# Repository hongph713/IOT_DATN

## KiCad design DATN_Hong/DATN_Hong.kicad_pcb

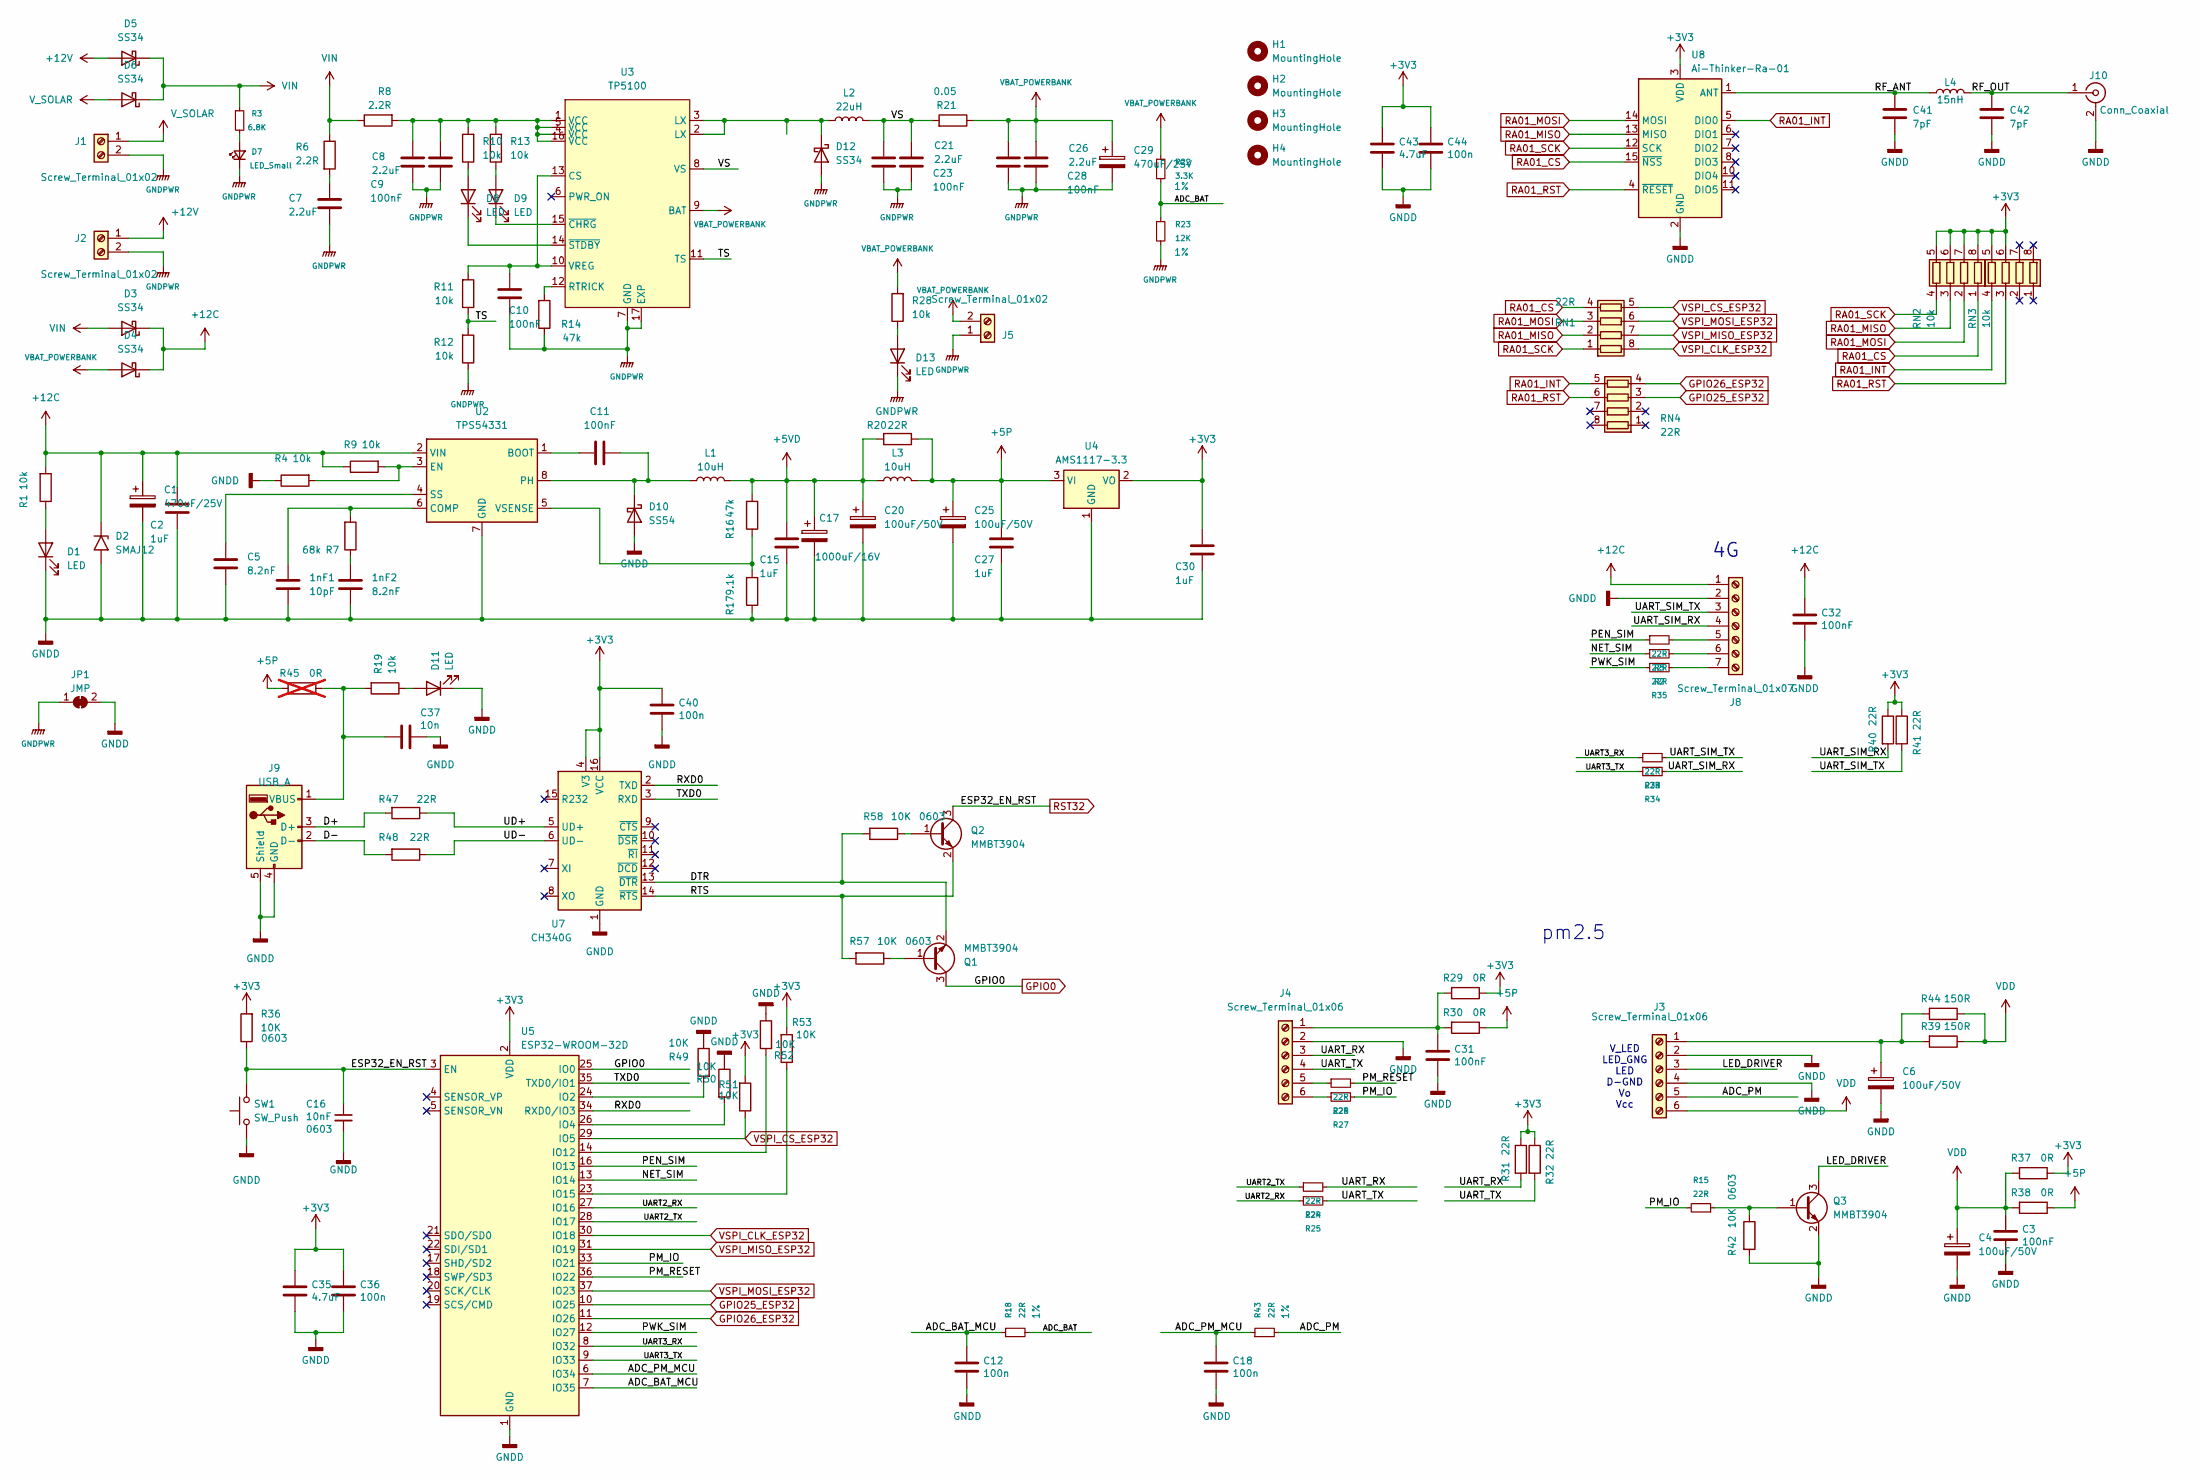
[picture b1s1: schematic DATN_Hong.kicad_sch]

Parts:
1nF1: 10pF; C_0603_1608Metric
1nF2: 8.2nF; C_0603_1608Metric
C1, C29: 470uF/25V; CP_Elec_10x10.5
C2, C15, C27, C30: 1uF; C_1206_3216Metric
C3, C31, C32: 100nF; C_0603_1608Metric; Part Description 10uF 10% 10V Ceramic Capacitor X7R 0805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
C4, C6, C20, C25: 100uF/50V; CP_EIA-7343-15_Kemet-W
C5: 8.2nF; C_0603_1608Metric
C7, C8, C21, C26: 2.2uF; C_1206_3216Metric
C9, C10, C11, C23, C28: 100nF; C_0603_1608Metric
C12, C18, C36, C44: 100n; C_0603_1608Metric; PART#1 G030617
C16: 10nF; C_0603_1608Metric; VOLTAGE 25V; PART#1 C021101
C17: 1000uF/16V; CP_Elec_10x10
C35, C43: 4.7uF; C_1206_3216Metric; PART#1 C020609
C37: 10n; C_0603_1608Metric
C40: 100n; C_0603_1608Metric
C41, C42: 7pF; C_0603_1608Metric
D1, D8, D9, D11, D13: LED; LED_0603_1608Metric
D2: SMAJ12; D_SMA
D3, D4, D5, D6, D12: SS34; D_SMA
D7: LED_Small; LED_0603_1608Metric
D10: SS54; D_SMA
H1, H2, H3, H4: MountingHole; MountingHole_3.2mm_M3
J1, J2, J5: Screw_Terminal_01x02; JST_VH_B2P-VH-B_1x02_P3.96mm_Vertical
J3, J4: Screw_Terminal_01x06; TerminalBlock_Xinya_XY308-2.54-6P_1x06_P2.54mm_Horizontal
J8: Screw_Terminal_01x07; PinHeader_1x07_P2.54mm_Vertical
J9: USB_A; USB_B_OST_USB-B1HSxx_Horizontal
J10: Conn_Coaxial; SMA_Amphenol_132291-12_Vertical
JP1: JMP; SolderJumper-2_P1.3mm_Bridged2Bar_RoundedPad1.0x1.5mm
L1: 10uH; L_12x12mm_H8mm
L2: 22uH; L_10.4x10.4_H4.8
L3: 10uH; L_Bourns-SRN4018
L4: 15nH; L_0603_1608Metric
Q1, Q2, Q3: MMBT3904; SOT-23
R1, R4, R9, R10, R11, R12, R13, R19, R28: 10k; R_0603_1608Metric
R2, R5, R15, R18, R24, R25, R26, R27, R33, R34, R35, R43, R47, R48: 22R; R_0603_1608Metric
R3: 6.8K; R_0603_1608Metric
R6, R8: 2.2R; R_1206_3216Metric
R7: 68k; R_0603_1608Metric
R14, R16: 47k; R_0603_1608Metric
R17: 9.1k; R_0603_1608Metric
R20: 22R; R_1206_3216Metric
R21: 0.05; R_1206_3216Metric
R22: 3.3K; R_0603_1608Metric; PART CLA0759
R23: 12K; R_0603_1608Metric
R29, R30, R37, R38: 0R; R_0603_1608Metric; Part Description Resistor 510K M1005 1% 63mW
R31, R32, R40, R41: 22R; R_0603_1608Metric; Part Description Resistor 510K M1005 1% 63mW
R36, R42, R49, R50, R51, R52, R53, R57, R58: 10K; R_0603_1608Metric
R39: 150R; R_1206_3216Metric; Part Description Resistor 510K M1005 1% 63mW
R44: 150R; R_Axial_DIN0207_L6.3mm_D2.5mm_P7.62mm_Horizontal; Part Description Resistor 510K M1005 1% 63mW
R45: 0R; R_0603_1608Metric; Part Description Resistor 510K M1005 1% 63mW; not fitted
RN1, RN4: 22R; R_Array_Convex_4x0603
RN2, RN3: 10k; R_Array_Convex_4x0603
SW1: SW_Push; SW_SPST_CK_RS282G05A3
U2: TPS54331; SOIC-8_3.9x4.9mm_P1.27mm
U3: TP5100; QFN-16-1EP_4x4mm_P0.65mm_EP2.1x2.1mm_ThermalVias
U4: AMS1117-3.3; SOT-223-3_TabPin2
U5: ESP32-WROOM-32D
U7: CH340G; SOIC-16_3.9x9.9mm_P1.27mm
U8: Ai-Thinker-Ra-01; Ai-Thinker-Ra-01-LoRa

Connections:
+3V3: C30.1, C35.1, C36.1, C40.1, C43.1, C44.1, R29.1, R31.1, R32.1, R36.2, R37.1, R40.1, R41.1, R51.2, R53.2, RN2.5 (R4.2), RN2.6 (R3.2), RN2.7 (R2.2), RN2.8 (R1.2), RN3.5 (R4.2), RN3.6 (R3.2), U4.2 (VO), U5.2 (VDD), U7.4 (V3), U7.16 (VCC), U8.3 (VDD)
+5P: C25.1, C27.1, L3.2, R20.2, R30.1, R38.1, R45.2, U4.3 (VI)
+5VD: C15.1, C17.1, C20.1, L1.2, L3.1, R16.2, R20.1
+12C: C1.1, C2.1, C32.1, D2.1 (A1), D3.1 (K), D4.1 (K), J8.1, R1.2, R9.1, U2.2 (VIN)
+12V: D5.2 (A), J2.1
/ADC_BAT: R18.2, R22.2, R23.1
/ADC_BAT_MCU: C12.1, R18.1, U5.7 (IO35)
/ADC_PM: J3.5, R43.2
/ADC_PM_MCU: C18.1, R43.1, U5.6 (IO34)
/D+: J9.3 (D+), R47.2
/D-: J9.2 (D-), R48.2
/DTR: Q1.2 (E), R58.2, U7.13 (~DTR)
/LED_DRIVER: J3.3, Q3.3 (C)
/NET_SIM: R2.1, U5.13 (IO14)
/PEN_SIM: R5.1, U5.16 (IO13)
/PM_IO: R15.2, R27.2, U5.33 (IO21)
/PM_RESET: R26.2, U5.36 (IO22)
/PWK_SIM: R35.1, U5.12 (IO27)
/RF_ANT: C41.1, L4.1, U8.1 (ANT)
/RF_OUT: C42.1, J10.1 (In), L4.2
/RTS: Q2.2 (E), R57.2, U7.14 (~RTS)
/RXD0: U5.34 (RXD0/IO3), U7.2 (TXD)
/TS: R11.1, R12.2, U3.11 (TS)
/TXD0: U5.35 (TXD0/IO1), U7.3 (RXD)
/UART2_RX: R25.1, U5.27 (IO16)
/UART2_TX: R24.1, U5.28 (IO17)
/UART3_RX: R33.1, U5.8 (IO32)
/UART3_TX: R34.1, U5.9 (IO33)
/UART_RX: J4.3, R24.2, R31.2
/UART_SIM_RX: J8.4, R34.2, R40.2
/UART_SIM_TX: J8.3, R33.2, R41.2
/UART_TX: J4.4, R25.2, R32.2
/UD+: R47.1, U7.5 (UD+)
/UD-: R48.1, U7.6 (UD-)
/VS: C21.1, C23.2, L2.2, R21.2, U3.8 (VS)
GNDD: 1nF1.2, 1nF2.2, C1.2, C2.2, C3.2, C4.2, C5.2, C6.2, C12.2, C15.2, C16.2, C17.2, C18.2, C20.2, C25.2, C27.2, C30.2, C31.2, C32.2, C35.2, C36.2, C37.1, C40.2, C41.2, C42.2, C43.2, C44.2, D1.1 (K), D2.2 (A2), D10.2 (A), D11.1 (K), J3.2, J3.4, J4.2, J8.2, J9.4 (GND), J9.5 (Shield), J10.2 (Ext), JP1.2 (B), Q3.2 (E), R4.1, R17.1, R42.2, R49.1, R50.1, R52.1, SW1.1, U2.7 (GND), U4.1 (GND), U5.1 (GND), U5.15 (GND), U5.38 (GND), U5.39 (GND), U7.1 (GND), U8.2 (GND), U8.9 (GND), U8.16 (GND)
GNDPWR: C7.2, C8.2, C9.1, C10.1, C21.2, C23.1, C26.2, C28.1, C29.2, D7.1 (K), D12.2 (A), D13.1 (K), J1.2, J2.2, J5.1, JP1.1 (A), R12.1, R14.1, R23.2, U3.7 (GND), U3.17 (EXP)
GPIO0: Q1.3 (C), U5.25 (IO0)
GPIO25_ESP32: RN4.3 (R3.1), U5.10 (IO25)
GPIO26_ESP32: RN4.4 (R4.1), U5.11 (IO26)
unnamed: 1nF2.1, R7.1
unnamed: C7.1, R6.2
unnamed: C8.1, C9.2, R8.2, R10.2, R13.2, U3.1 (VCC), U3.4 (VCC), U3.5 (VCC), U3.16 (VCC)
unnamed: D1.2 (A), R1.1
unnamed: D7.2 (A), R3.2
unnamed: D8.2 (A), R10.1
unnamed: D8.1 (K), U3.14 (~STDBY)
unnamed: D9.2 (A), R13.1
unnamed: D9.1 (K), U3.15 (~CHRG)
unnamed: C11.2, D10.1 (K), L1.1, U2.8 (PH)
unnamed: D11.2 (A), R19.1
unnamed: D12.1 (K), L2.1, U3.2 (LX), U3.3 (LX)
unnamed: D13.2 (A), R28.1
unnamed: C6.1, J3.1, R39.2, R44.2
unnamed: C31.1, J4.1, R29.2, R30.2
unnamed: J4.5, R26.1
unnamed: J4.6, R27.1
unnamed: J8.5, R5.2
unnamed: J8.6, R2.2
unnamed: J8.7, R35.2
unnamed: C37.2, J9.1 (VBUS), R19.2, R45.1
unnamed: Q1.1 (B), R57.1
unnamed: Q2.1 (B), R58.1
unnamed: Q3.1 (B), R15.1, R42.1
unnamed: C11.1, U2.1 (BOOT)
unnamed: 1nF1.1, R7.2, U2.6 (COMP)
unnamed: R4.2, R9.2, U2.3 (EN)
unnamed: C5.1, U2.4 (SS)
unnamed: R16.1, R17.2, U2.5 (VSENSE)
unnamed: C10.2, R11.2, U3.10 (VREG), U3.13 (CS)
unnamed: R14.2, U3.12 (RTRICK)
unnamed: R49.2, U5.24 (IO2)
unnamed: R50.2, U5.26 (IO4)
unnamed: R52.2, U5.14 (IO12)
unnamed: R53.1, U5.23 (IO15)
RA01_CS: RN1.4 (R4.1), RN2.1 (R1.1), U8.15 (~NSS)
RA01_INT: RN3.4 (R4.1), RN4.5 (R4.2), U8.5 (DIO0)
RA01_MISO: RN1.2 (R2.1), RN2.3 (R3.1), U8.13 (MISO)
RA01_MOSI: RN1.3 (R3.1), RN2.2 (R2.1), U8.14 (MOSI)
RA01_RST: RN3.3 (R3.1), RN4.6 (R3.2), U8.4 (~RESET)
RA01_SCK: RN1.1 (R1.1), RN2.4 (R4.1), U8.12 (SCK)
RST32: C16.1, Q2.3 (C), R36.1, SW1.2, U5.3 (EN)
VBAT_POWERBANK: C26.1, C28.2, C29.1, D4.2 (A), J5.2, R21.1, R22.1, R28.2, U3.9 (BAT)
VDD: C3.1, C4.1, J3.6, R37.2, R38.2, R39.1, R44.1
VIN: D3.2 (A), D5.1 (K), D6.1 (K), R3.1, R6.1, R8.1
VSPI_CLK_ESP32: RN1.8 (R1.2), U5.30 (IO18)
VSPI_CS_ESP32: R51.1, RN1.5 (R4.2), U5.29 (IO5)
VSPI_MISO_ESP32: RN1.7 (R2.2), U5.31 (IO19)
VSPI_MOSI_ESP32: RN1.6 (R3.2), U5.37 (IO23)
V_SOLAR: D6.2 (A), J1.1

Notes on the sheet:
V_LED LED_GNG LED D-GND Vo Vcc
pm2.5

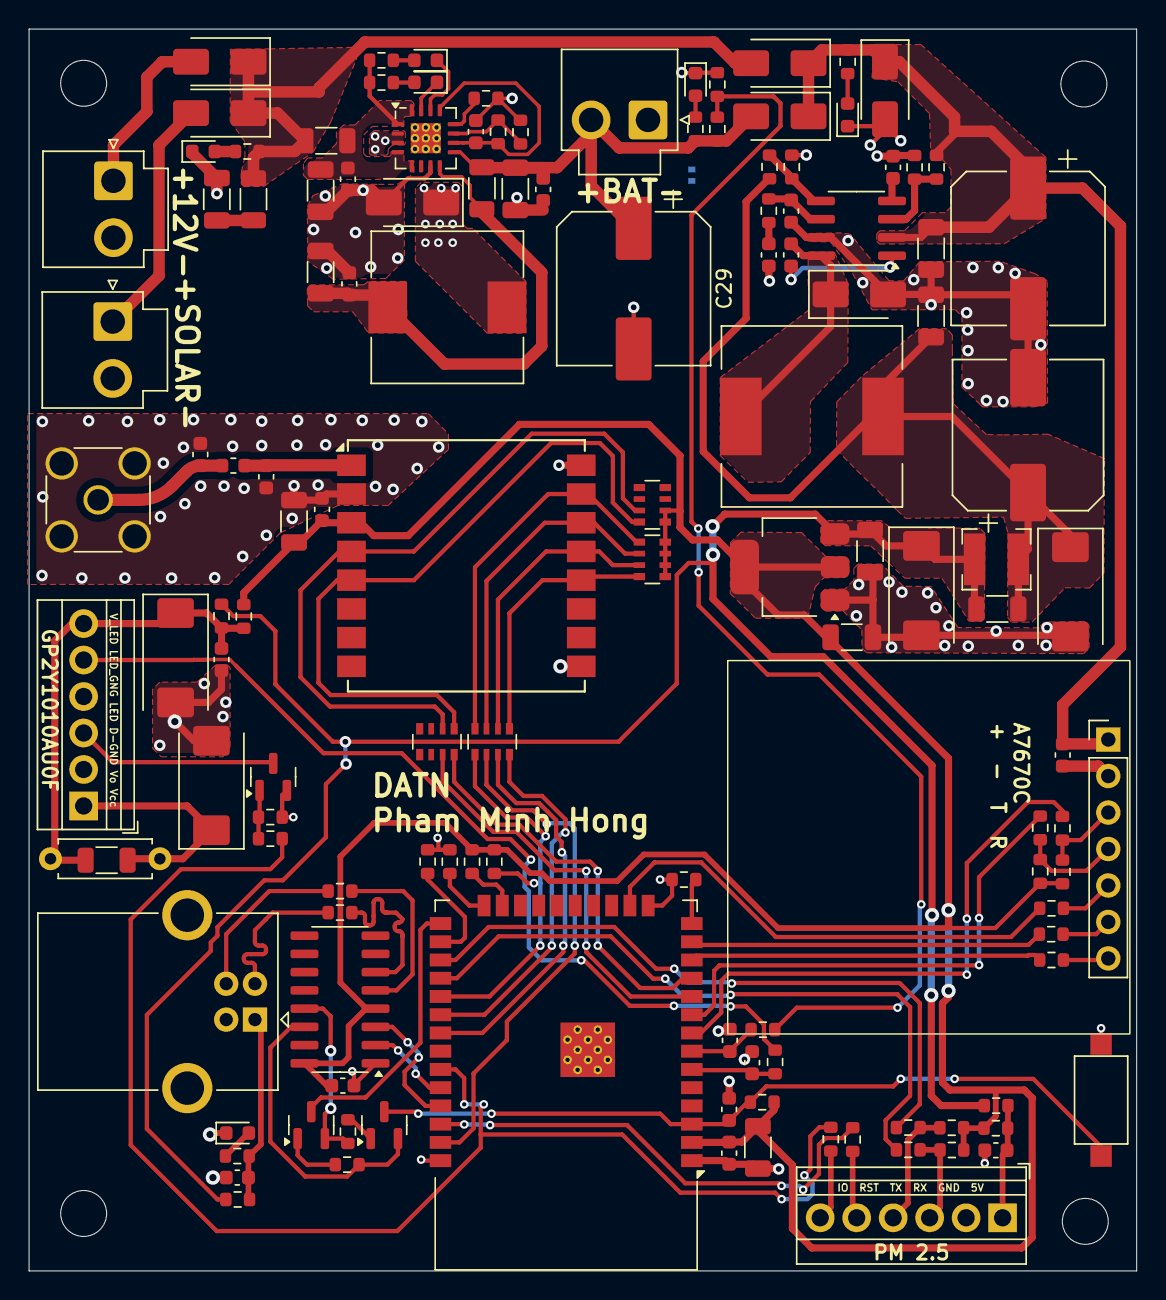
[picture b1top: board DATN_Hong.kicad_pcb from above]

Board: 2 copper layers, 77.1 x 86.5 mm, 135 parts (1 on the bottom side), 90 nets.

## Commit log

2025-06-25 upload code iot
